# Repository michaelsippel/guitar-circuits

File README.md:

# guitar-circuits
My custom guitar schematics and PCBs.

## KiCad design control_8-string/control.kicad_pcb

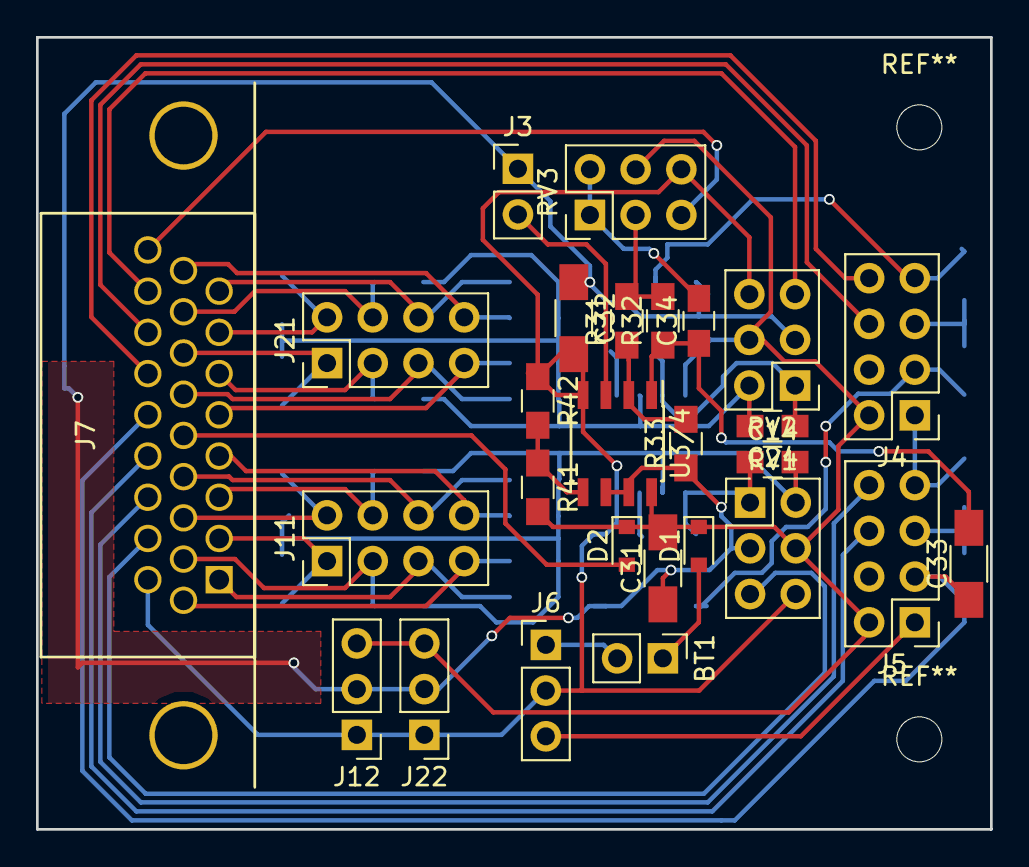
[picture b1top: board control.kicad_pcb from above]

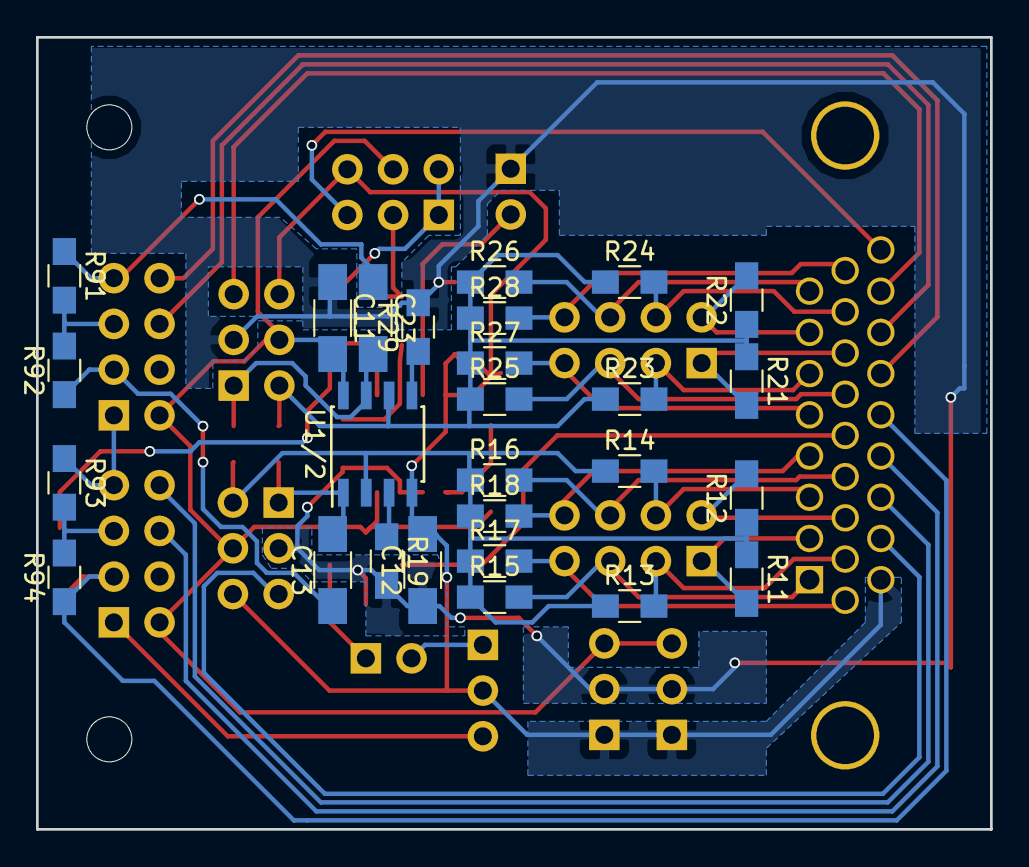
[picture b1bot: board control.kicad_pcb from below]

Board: 2 copper layers, 53.0 x 44.0 mm, 54 parts (27 on the bottom side), 48 nets.

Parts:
BT1: Battery; Pin_Header_Straight_1x02_Pitch2.54mm
C11, C12, C13, C23, C31, C32, C33: C; C_1206_HandSoldering
C14, C24, C34: C; C_0805_HandSoldering
D1, D2: D; D_0805
J3: CONN_01X02; Pin_Header_Straight_1x02_Pitch2.54mm
J4, J5, J11, J21: CONN_02X04; Pin_Header_Straight_2x04_Pitch2.54mm
J6: JACK_2P; Pin_Header_Straight_1x03_Pitch2.54mm
J7: DIL_26; DA26
J12, J22: CONN_01X03; Pin_Header_Straight_1x03_Pitch2.54mm
R11, R12, R13, R14, R15, R16, R17, R18, R19, R21, R22, R23, R24, R25, R26, R27, R28, R29, R31, R32, R33, R41, R42, R91, R92, R93, R94: R; R_0805_HandSoldering
RV1, RV2, RV3: POT_Dual; Pin_Header_Straight_2x03_Pitch2.54mm
U1/2, U3/4: TL072; SOIC-8_3.9x4.9mm_Pitch1.27mm

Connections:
+9V: C11.2, C31.2, D1.1, D2.1, J4.2, J5.2, J12.3, J22.3, R41.2, RV1.4, RV2.4, RV3.4, U1/2.8, U3/4.8
-9VA: C12.2, C32.2, J6.2, J7.25, J12.1, J22.1, R42.1, RV1.6, RV2.6, RV3.6, U1/2.4, U3/4.4
GND: C11.1, C12.1, C31.1, C32.1, J3.1, J12.2, J22.2, R19.2, R29.2, R33.1, RV1.3, RV2.3, U3/4.6, U3/4.7
unnamed: BT1.1, D1.2
unnamed: BT1.2, J6.1
unnamed: C13.1, J4.3, R92.1
unnamed: C13.2, C14.1, RV1.1, U1/2.1
unnamed: C14.2, R11.1, R12.1, R13.1, R14.1, R15.1, R16.1, R17.1, R18.1, RV1.2, U1/2.2
unnamed: C23.1, J4.7, R91.1
unnamed: C23.2, C24.1, RV2.1, U1/2.7
unnamed: C24.2, R21.1, R22.1, R23.1, R24.1, R25.1, R26.1, R27.1, R28.1, RV2.2, U1/2.6
unnamed: C33.1, J5.3, J7.24, R94.1
unnamed: C33.2, C34.1, R32.1, U3/4.1
unnamed: C34.2, RV3.1, RV3.2
unnamed: D2.2, J7.26
unnamed: J3.2, U3/4.3
unnamed: J4.1, J5.7, R93.1
unnamed: J4.5, R91.2, R92.2
unnamed: J4.6, J7.12
unnamed: J4.8, J7.13
unnamed: J5.1, J6.3
unnamed: J5.5, R93.2, R94.2
unnamed: J5.6, J7.10
unnamed: J5.8, J7.11
unnamed: J7.9, RV1.5
unnamed: J7.22, RV2.5
unnamed: J7.23, RV3.5
unnamed: J7.1, J11.1, R11.2
unnamed: J7.2, J11.2, R12.2
unnamed: J7.3, J11.3, R13.2
unnamed: J7.4, J11.4, R14.2
unnamed: J7.5, J11.5, R15.2
unnamed: J7.6, J11.6, R16.2
unnamed: J7.7, J11.7, R17.2
unnamed: J7.8, J11.8, R18.2
unnamed: J7.14, J21.1, R21.2
unnamed: J7.15, J21.2, R22.2
unnamed: J7.16, J21.3, R23.2
unnamed: J7.17, J21.4, R24.2
unnamed: J7.18, J21.5, R25.2
unnamed: J7.19, J21.6, R26.2
unnamed: J7.20, J21.7, R27.2
unnamed: J7.21, J21.8, R28.2
unnamed: R19.1, U1/2.3
unnamed: R29.1, U1/2.5
unnamed: R31.1, R33.2, U3/4.2
unnamed: R31.2, R32.2, RV3.3
unnamed: R41.1, R42.2, U3/4.5

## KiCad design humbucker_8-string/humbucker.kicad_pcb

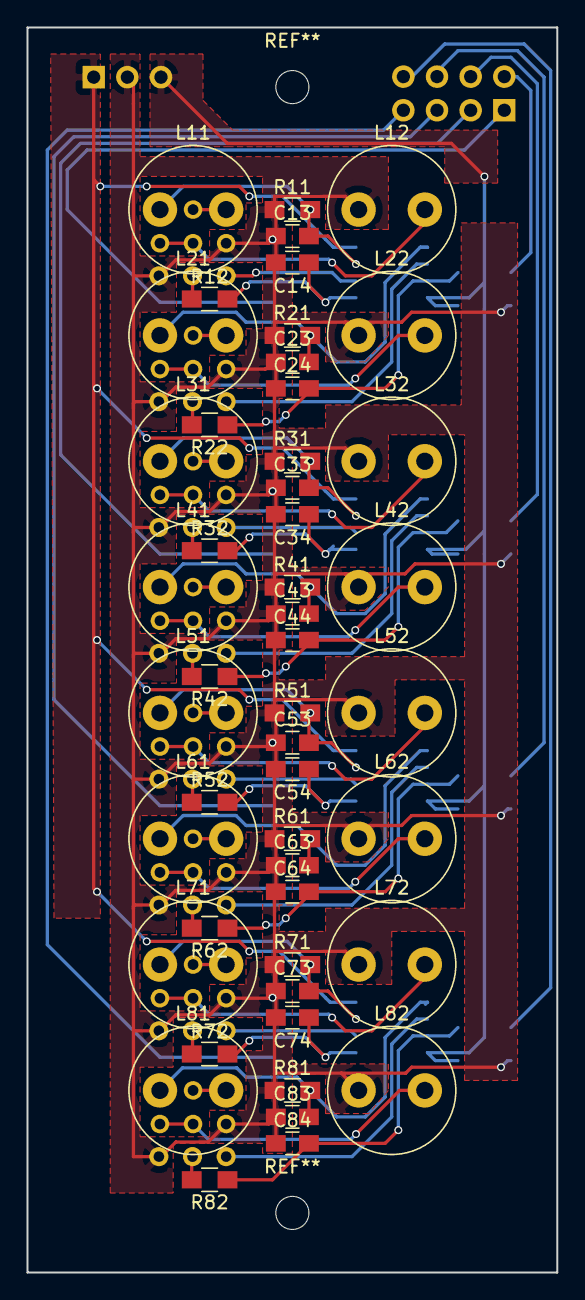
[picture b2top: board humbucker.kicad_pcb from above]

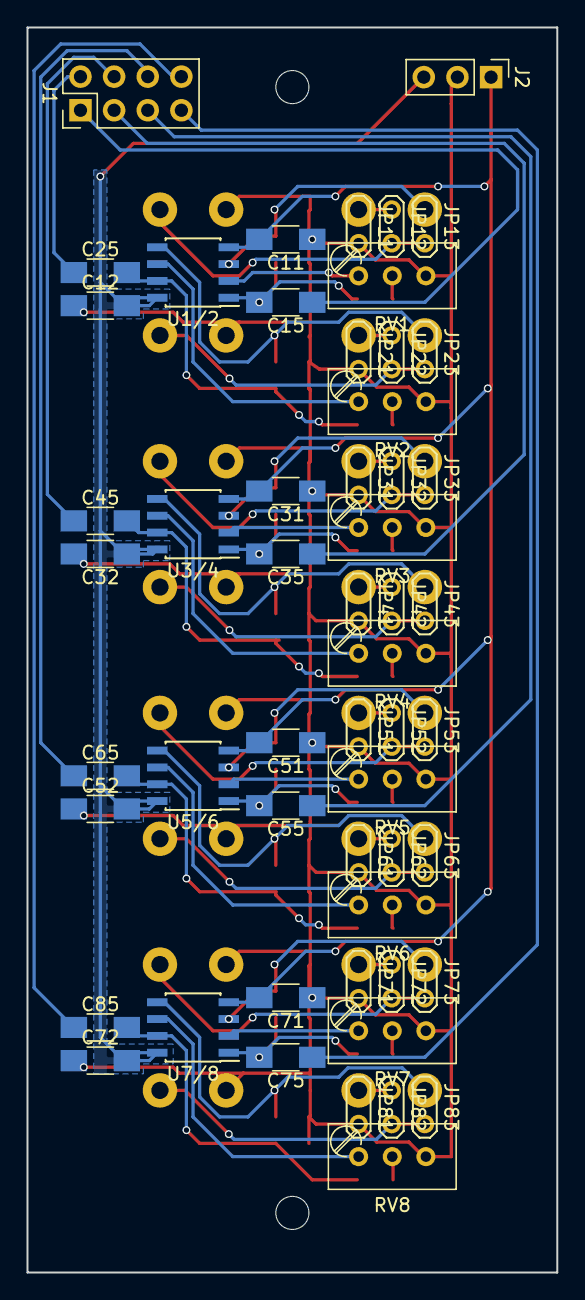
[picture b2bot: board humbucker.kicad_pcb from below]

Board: 2 copper layers, 40.0 x 94.0 mm, 102 parts (54 on the bottom side), 59 nets.

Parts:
C11, C12, C15, C25, C31, C32, C35, C45, C51, C52, C55, C65, C71, C72, C75, C85: C; C_1206_HandSoldering
C13, C14, C23, C24, C33, C34, C43, C44, C53, C54, C63, C64, C73, C74, C83, C84: C; C_0805_HandSoldering
J1: CONN_02X04; Pin_Header_Straight_2x04_Pitch2.54mm
J2: CONN_01X03; Pin_Header_Straight_1x03_Pitch2.54mm
JP11, JP13, JP21, JP23, JP31, JP33, JP41, JP43, JP51, JP53, JP61, JP63, JP71, JP73, JP81, JP83: Jumper_NC_Small; Test_Point_2Pads
JP12, JP22, JP32, JP42, JP52, JP62, JP72, JP82: Jumper_NO_Small; Test_Point_2Pads
L11, L12, L21, L22, L31, L32, L41, L42, L51, L52, L61, L62, L71, L72, L81, L82: L; L_Radial_D9.5mm_P5.00mm_Fastron_07HVP
R11, R12, R21, R22, R31, R32, R41, R42, R51, R52, R61, R62, R71, R72, R81, R82: R; R_0805_HandSoldering
RV1, RV2, RV3, RV4, RV5, RV6, RV7, RV8: POT; Potentiometer_Trimmer_Bourns_3296W
U1/2, U3/4, U5/6, U7/8: TL072; SOIC-8_3.9x4.9mm_Pitch1.27mm

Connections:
+9V: C12.2, C32.1, C52.2, C72.2, J2.3, U1/2.8, U3/4.8, U5/6.8, U7/8.8
-9VA: C11.2, C31.2, C51.2, C71.2, J2.1, U1/2.4, U3/4.4, U5/6.4, U7/8.4
GND: C11.1, C12.1, C13.1, C14.2, C23.1, C24.1, C31.1, C32.2, C33.1, C34.2, C43.1, C44.1, C51.1, C52.1, C53.1, C54.2, C63.1, C64.1, C71.1, C72.1, C73.1, C74.2, C83.1, C84.1, J2.2, JP11.2, JP21.2, JP31.2, JP41.2, JP51.2, JP61.2, JP71.2, JP81.2, L12.1, L22.1, L32.1, L42.1, L52.1, L62.1, L72.1, L82.1, R11.1, R21.1, R31.1, R41.1, R51.1, R61.1, R71.1, R81.1, RV1.3, RV2.3, RV3.3, RV4.3, RV5.3, RV6.3, RV7.3, RV8.3
unnamed: C13.2, JP13.1, L11.1, R11.2, U1/2.3
unnamed: C14.1, C15.2, R12.2, U1/2.1
unnamed: C15.1, J1.1
unnamed: C23.2, JP23.1, L21.1, R21.2, U1/2.5
unnamed: C24.2, C25.2, R22.1, U1/2.7
unnamed: C25.1, J1.2
unnamed: C33.2, JP33.1, L31.1, R31.2, U3/4.3
unnamed: C34.1, C35.2, R32.2, U3/4.1
unnamed: C35.1, J1.3
unnamed: C43.2, JP43.1, L41.1, R41.2, U3/4.5
unnamed: C44.2, C45.2, R42.1, U3/4.7
unnamed: C45.1, J1.4
unnamed: C53.2, JP53.1, L51.1, R51.2, U5/6.3
unnamed: C54.1, C55.2, R52.2, U5/6.1
unnamed: C55.1, J1.5
unnamed: C63.2, JP63.1, L61.1, R61.2, U5/6.5
unnamed: C64.2, C65.2, R62.1, U5/6.7
unnamed: C65.1, J1.6
unnamed: C73.2, JP73.1, L71.1, R71.2, U7/8.3
unnamed: C74.1, C75.2, R72.2, U7/8.1
unnamed: C75.1, J1.7
unnamed: C83.2, JP83.1, L81.1, R81.2, U7/8.5
unnamed: C84.2, C85.2, R82.1, U7/8.7
unnamed: C85.1, J1.8
unnamed: JP11.1, JP12.1, L11.2
unnamed: JP12.2, JP13.2, L12.2
unnamed: JP21.1, JP22.1, L21.2
unnamed: JP22.2, JP23.2, L22.2
unnamed: JP31.1, JP32.1, L31.2
unnamed: JP32.2, JP33.2, L32.2
unnamed: JP41.1, JP42.1, L41.2
unnamed: JP42.2, JP43.2, L42.2
unnamed: JP51.1, JP52.1, L51.2
unnamed: JP52.2, JP53.2, L52.2
unnamed: JP61.1, JP62.1, L61.2
unnamed: JP62.2, JP63.2, L62.2
unnamed: JP71.1, JP72.1, L71.2
unnamed: JP72.2, JP73.2, L72.2
unnamed: JP81.1, JP82.1, L81.2
unnamed: JP82.2, JP83.2, L82.2
unnamed: R12.1, RV1.2
unnamed: R22.2, RV2.2
unnamed: R32.1, RV3.2
unnamed: R42.2, RV4.2
unnamed: R52.1, RV5.2
unnamed: R62.2, RV6.2
unnamed: R72.1, RV7.2
unnamed: R82.2, RV8.2
unnamed: RV1.1, U1/2.2
unnamed: RV2.1, U1/2.6
unnamed: RV3.1, U3/4.2
unnamed: RV4.1, U3/4.6
unnamed: RV5.1, U5/6.2
unnamed: RV6.1, U5/6.6
unnamed: RV7.1, U7/8.2
unnamed: RV8.1, U7/8.6

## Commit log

2017-03-21 humbucker schematics
2017-03-28 add jumpers for wiring humbucker in parallel/serial
2017-03-30 add plotted schematic
2017-04-03 humbucker PCB
2017-04-09 humbucker fix
2017-04-17 add 8-string control & mix schematic
2017-04-18 control: buffered virtual ground
2017-04-18 control: lowpass filter for piezo buffer & annotations
2017-04-18 humbucker: add mounting holes & dimensions
2017-04-19 add humbcker renders
2017-04-22 add DA-26 footprint
2017-04-22 control: footprints
2017-04-23 control PCB
2017-04-25 add edge cuts
